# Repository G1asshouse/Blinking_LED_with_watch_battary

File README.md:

View this project on [CADLAB.io](https://cadlab.io/project/1289). 

# Blinking_LED_with_watch_battary
 Overview - Two LEDs are powered by a single watch battery. A 555 timer is used to generate the pulse timing for the two LEDs. Board + 2-sided board + through-holes ++ Vias, ground stitching, battery holder's alignment/relief tabs. Parts + All surface-mount parts

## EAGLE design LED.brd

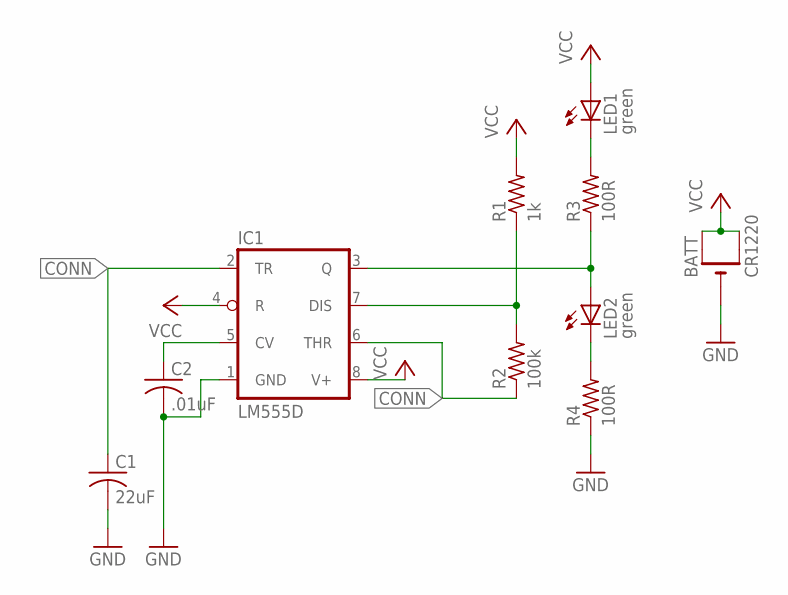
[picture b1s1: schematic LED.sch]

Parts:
BATT: CR1220; CR1220-SMD
C1: 22uF; C0805
C2: .01uF; C0805
IC1: LM555D; SO08
LED1, LED2: green; CHIPLED_0805
R1: 1k; R0805
R2: 100k; R0805
R3, R4: 100R; R0805

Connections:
CONN: C1.1, IC1.2 (TR), IC1.6 (THR), R2.1
GND: BATT.-, C1.2, C2.2, IC1.1 (GND), R4.1
unnamed: C2.1, IC1.5 (CV)
unnamed: IC1.7 (DIS), R1.1, R2.2
unnamed: LED1.C, R3.2
unnamed: IC1.3 (Q), LED2.A, R3.1
unnamed: LED2.C, R4.2
VCC: BATT.+$1 (+), BATT.+$2 (+1), IC1.4 (R), IC1.8 (V+), LED1.A, R1.2

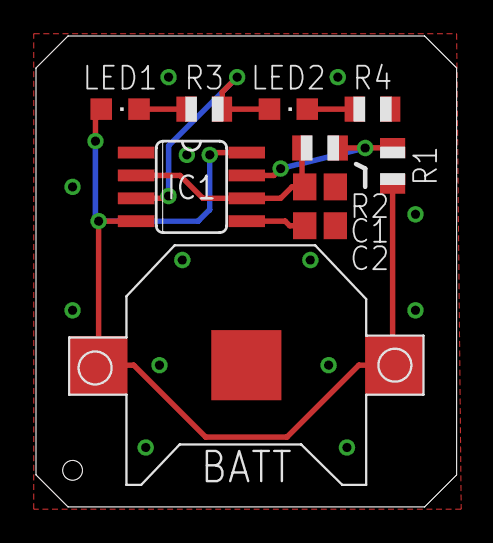
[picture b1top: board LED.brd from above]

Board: 2 copper layers, 23.4 x 26.2 mm, 10 parts (0 on the bottom side), 8 nets.

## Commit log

2018-09-10 Inital commit.
2018-09-10 Backlink to CADLAB.io has been added.
